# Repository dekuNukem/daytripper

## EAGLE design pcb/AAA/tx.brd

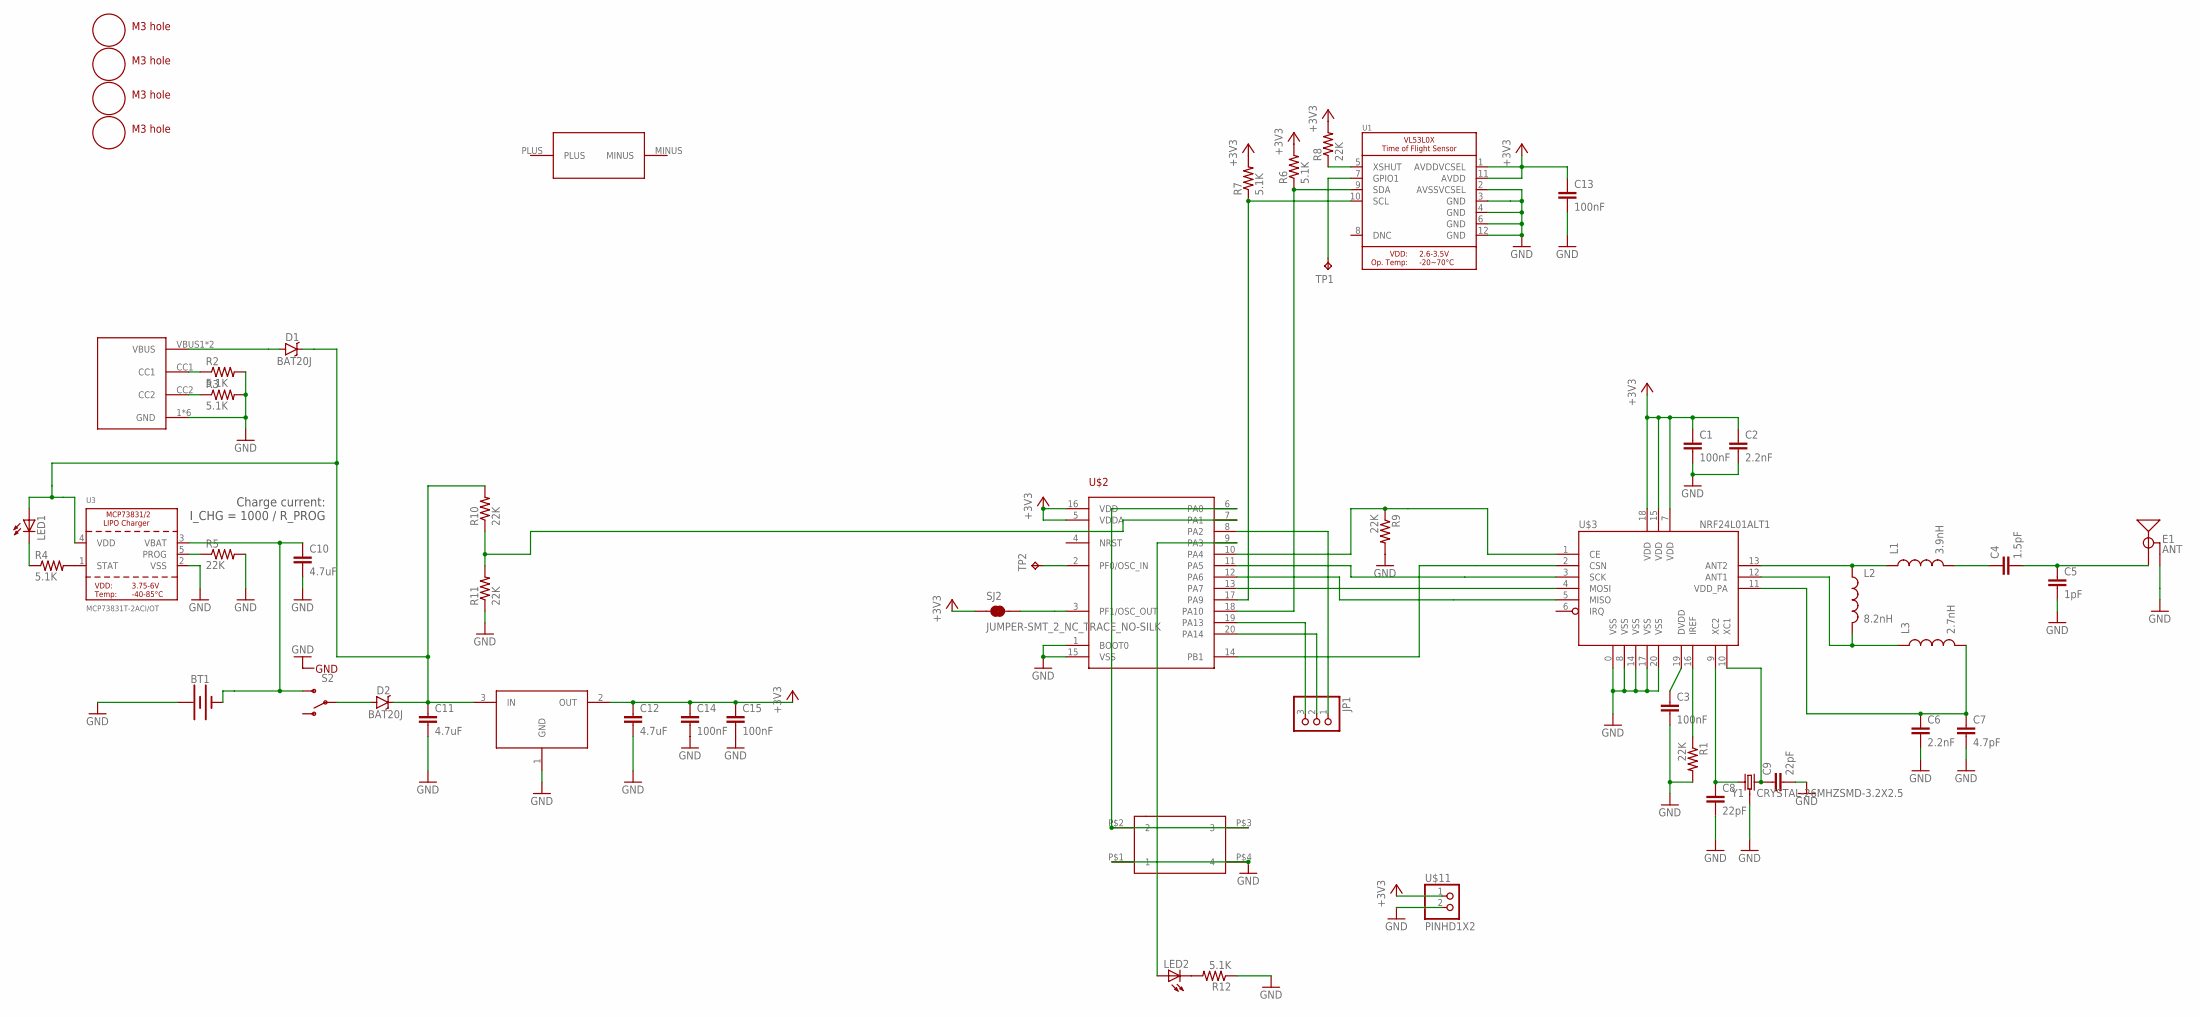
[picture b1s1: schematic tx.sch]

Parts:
BT1: TX_SPARKFUN-BATTERIES_BATTERY-24.5MM_PTH; TX_SPARKFUN-BATTERIES_BATTCON_24.5MM_PTH
C1, C3, C13, C14, C15: 100nF; 0805
C2, C6: 2.2nF; 0805
C4: 1.5pF; 0805
C5: 1pF; 0805
C7: 4.7pF; 0805
C8, C9: 22pF; 0805
C10, C11, C12: 4.7uF; 0805
D1, D2: BAT20J; SOD-323
E1: ANT; TRACE_ANTENNA_2.4GHZ_15.2MM
JP1: PINHD-1X3CB; 1X03-CLEANBIG
L1: 3.9nH; 0805
L2: 8.2nH; 0805
L3: 2.7nH; 0805
LED1, LED2: LEDCHIP-LED0805; CHIP-LED0805
R1, R5, R8, R9, R10, R11: 22K; 0805
R2, R3, R4, R6, R7, R12: 5.1K; 0805
S2: SWITCH-SPDTTDFGDFG; SWITCH-SPST-SMD-A
SJ2: JUMPER-SMT_2_NC_TRACE_NO-SILK; SMT-JUMPER_2_NC_TRACE_NO-SILK
TP1, TP2: TPTP12R; TP12R
U1: VL53L0X; LGA12_ST
U3: MCP73831T-2ACI/OT; SOT23-5
U$1: L1_USBC_6P_DEV; L1_USBC_6P_PAC
U$2: STM32F030F4; TSSOP20
U$3: NRF24L01ALT1; QFN20_ALT1
U$4: AAA_SYM; AAAWTF
U$5, U$6, U$7, U$8: M3_MOUNTING_HOLE; M3_MOUNTING_HOLE_PACK
U$9: XC6206_DEV; SOT23R_INFINEON
U$10: 324_SW324_SWITCH_FOOT_HOLE; 342_SWICH_FOOT_HOLE
U$11: PINHD1X2; 1X02
Y1: CRYSTAL-26MHZSMD-3.2X2.5; CRYSTAL-SMD-3.2X2.5MM

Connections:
+3V3: C1.1, C2.1, C12.1, C13.1, C14.1, C15.1, R6.2, R7.2, R8.2, SJ2.1, U1.1 (AVDDVCSEL), U1.11 (AVDD), U$2.5 (VDDA), U$2.16 (VDD), U$3.7 (VDD), U$3.15 (VDD), U$3.18 (VDD), U$9.2 (OUT), U$11.1
GND: BT1.2 (+), C1.2, C2.2, C3.2, C5.2, C6.2, C7.2, C8.2, C9.2, C10.2, C11.2, C12.2, C13.2, C14.2, C15.2, E1.GND, R1.2, R2.2, R3.2, R5.2, R9.2, R11.1, R12.1, S2.G1 (GND), S2.G2 (GND), S2.G3 (GND), S2.G4 (GND), U1.2 (AVSSVCSEL), U1.3 (GND), U1.4 (GND), U1.6 (GND), U1.12 (GND), U3.2 (VSS), U$1.1 (GND), U$1.2 (GND), U$1.3 (GND), U$1.4 (GND), U$1.GND1 (GND), U$1.GND2 (GND), U$2.1 (BOOT0), U$2.15 (VSS), U$3.0 (VSS), U$3.8 (VSS), U$3.14 (VSS), U$3.17 (VSS), U$3.20 (VSS), U$9.1 (GND), U$10.P$1 (1), U$10.P$4 (4), U$11.2, Y1.2 (3), Y1.4 (3)
unnamed: C3.1, U$3.19 (DVDD)
unnamed: R1.1, U$3.16 (IREF)
unnamed: L1.1, L2.1, U$3.13 (ANT2)
unnamed: C4.1, L1.2
unnamed: C4.2, C5.1, E1.ANT (SIGNAL)
unnamed: L2.2, L3.1, U$3.12 (ANT1)
unnamed: C8.1, U$3.9 (XC2), Y1.1
unnamed: C6.1, C7.1, L3.2, U$3.11 (VDD_PA)
unnamed: C9.1, U$3.10 (XC1), Y1.3 (2)
unnamed: R3.1, U$1.CC2
unnamed: R2.1, U$1.CC1
unnamed: LED1.C, R4.1
unnamed: R4.2, U3.1 (STAT)
unnamed: U$2.13 (PA7), U$3.4 (MOSI)
unnamed: U$2.12 (PA6), U$3.5 (MISO)
unnamed: U$2.11 (PA5), U$3.3 (SCK)
unnamed: R5.1, U3.5 (PROG)
unnamed: R6.1, U1.9 (SDA), U$2.18 (PA10)
unnamed: D2.A, S2.2
unnamed: U$2.14 (PB1), U$3.2 (CSN)
unnamed: R9.1, U$2.10 (PA4), U$3.1 (CE)
unnamed: R7.1, U1.10 (SCL), U$2.17 (PA9)
unnamed: R8.1, U1.5 (XSHUT)
unnamed: BT1.1 (-), C10.1, S2.3 (S), U3.3 (VBAT)
unnamed: D1.A, U$1.VBUS1 (VBUS), U$1.VBUS2 (VBUS)
unnamed: C11.1, D1.C, D2.C, LED1.A, R10.2, U3.4 (VDD), U$9.3 (IN)
unnamed: LED2.C, R12.2
unnamed: LED2.A, U$2.9 (PA3)
unnamed: U$2.6 (PA0), U$10.P$2 (2), U$10.P$3 (3)
unnamed: JP1.3, U$2.19 (PA13)
unnamed: JP1.2, U$2.20 (PA14)
unnamed: JP1.1, U$2.8 (PA2)
unnamed: SJ2.2, U$2.3 (PF1/OSC_OUT)
unnamed: R10.1, R11.2, U$2.7 (PA1)
unnamed: TP1.TP, U1.7 (GPIO1)
unnamed: TP2.TP, U$2.2 (PF0/OSC_IN)

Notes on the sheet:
Charge current: I_CHG = 1000 / R_PROG

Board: 2 copper layers, 55 parts (4 on the bottom side), 38 nets, no tracks yet.

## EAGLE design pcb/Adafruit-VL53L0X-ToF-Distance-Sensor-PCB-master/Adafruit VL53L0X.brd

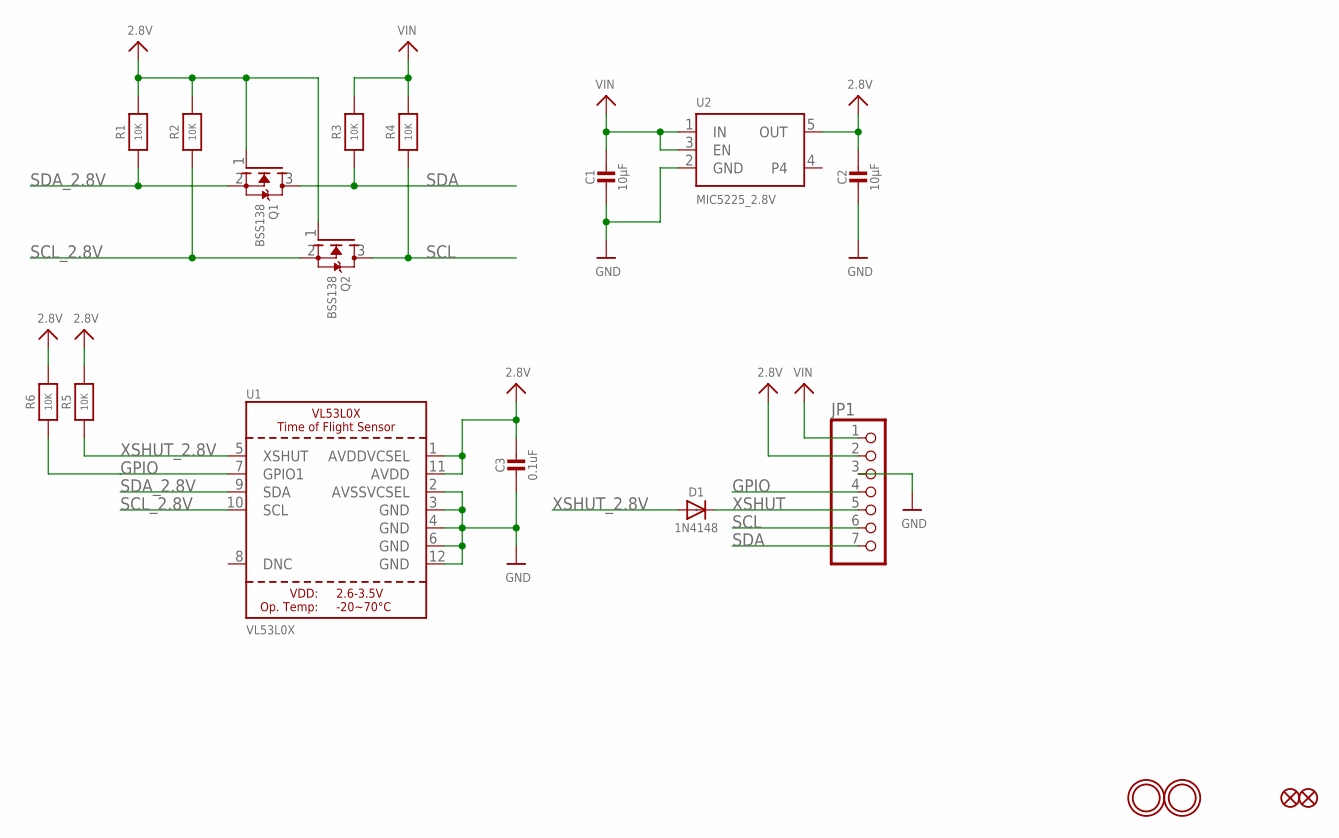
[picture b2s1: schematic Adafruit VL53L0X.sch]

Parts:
C1, C2: 10µF; 0805-NO
C3: 0.1uF; 0805-NO
D1: 1N4148; SOD-323
FID2, FID3: FIDUCIAL""; FIDUCIAL_1MM
JP1: HEADER-1X770MIL; 1X07_ROUND_70
Q1, Q2: BSS138; SOT23-WIDE
R1, R2, R3, R4, R5, R6: 10K; 0805-NO
U1: VL53L0X; LGA12_ST
U2: MIC5225_2.8V; SOT23-5
U$13, U$14: MOUNTINGHOLE2.5; MOUNTINGHOLE_2.5_PLATED

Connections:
2.8V: C2.1, C3.1, JP1.2, Q1.1 (G), Q2.1 (G), R1.2, R2.2, R5.2, R6.2, U1.1 (AVDDVCSEL), U1.11 (AVDD), U2.5 (OUT)
GND: C1.2, C2.2, C3.2, JP1.3, U1.2 (AVSSVCSEL), U1.3 (GND), U1.4 (GND), U1.6 (GND), U1.12 (GND), U2.2 (GND)
GPIO: JP1.4, R6.1, U1.7 (GPIO1)
SCL: JP1.6, Q2.3 (D), R4.1
SCL_2.8V: Q2.2 (S), R2.1, U1.10 (SCL)
SDA: JP1.7, Q1.3 (D), R3.1
SDA_2.8V: Q1.2 (S), R1.1, U1.9 (SDA)
VIN: C1.1, JP1.1, R3.2, R4.2, U2.1 (IN), U2.3 (EN)
XSHUT: D1.C, JP1.5
XSHUT_2.8V: D1.A, R5.1, U1.5 (XSHUT)

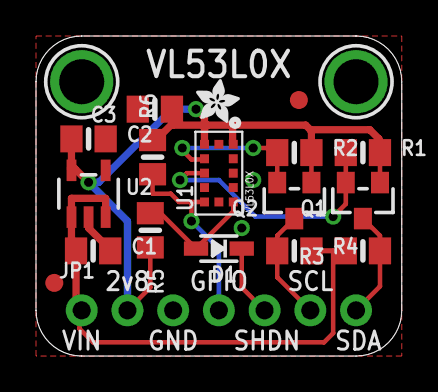
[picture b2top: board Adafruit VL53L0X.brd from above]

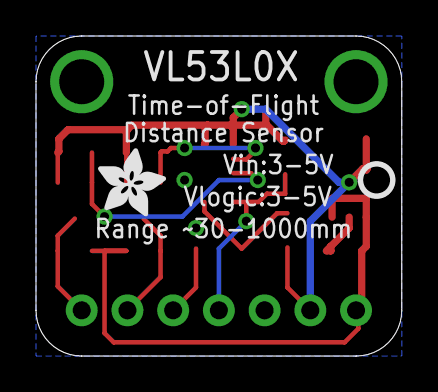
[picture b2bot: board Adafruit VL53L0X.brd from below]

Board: 2 copper layers, 20.3 x 17.8 mm, 22 parts (2 on the bottom side), 10 nets.

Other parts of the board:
U$12: PCBFEAT-REV-040
U$15: ADAFRUIT_3.5MM
U$18: ADAFRUIT_2.5MM

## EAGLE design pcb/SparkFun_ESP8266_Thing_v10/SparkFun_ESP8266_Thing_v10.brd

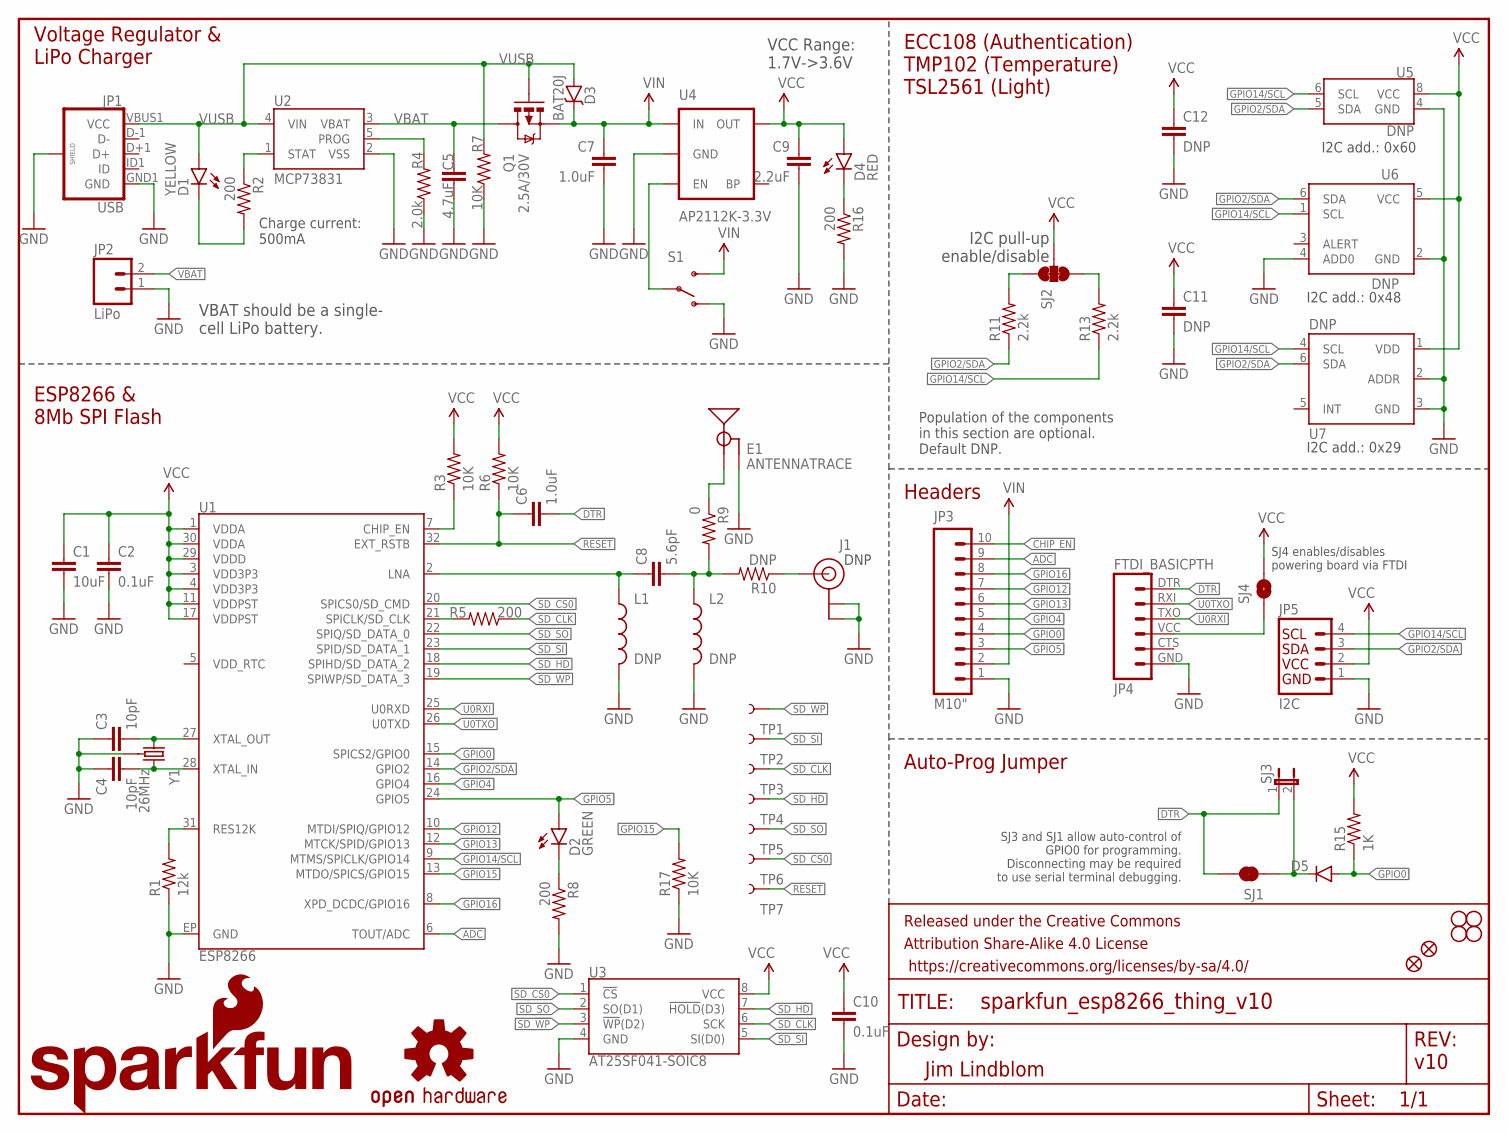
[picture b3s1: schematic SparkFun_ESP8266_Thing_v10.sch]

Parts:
C1: 10uF; 0603-CAP
C2, C10: 0.1uF; 0603-CAP
C3, C4: 10pF; 0603-CAP
C5: 4.7uF; 0603-CAP
C6: 1.0uF; 0603-CAP
C7: 1.0uF; 0805
C8: 5.6pF; 0603-CAP
C9: 2.2uF; 0603-CAP
C11, C12: DNP; 0603-CAP
D1: YELLOW; LED-0603
D2: GREEN; LED-0603
D3: BAT20J; SOD-323
D4: RED; LED-0603
D5: DIODEBAS16; SOD-323
E1: ANTENNATRACE; TRACE_ANTENNA_2.4GHZ_25.7MM
FID1, FID2: FIDUCIAL1X2; FIDUCIAL-1X2
FRAME1: FRAME-LETTER; CREATIVE_COMMONS
J1: DNP; U.FL
JP1: USB; USB-B-MICRO-SMD_V03
JP2: LiPo; JST-2-PTH
JP3: M10"; 1X10
JP4: FTDI_BASICPTH; FTDI_BASIC
JP5: I2C; 1X04
L1, L2: DNP; 0603
LOGO1: SFE_LOGO_NAME.2_INCH; SFE_LOGO_NAME_.2
LOGO3: SFE_LOGO_FLAME.1_INCH; SFE_LOGO_FLAME_.1
LOGO4: OSHW-LOGOS; OSHW-LOGO-S
Q1: 2.5A/30V; SOT23-3
R1: 12k; 0603-RES
R2, R5, R8, R16: 200; 0603-RES
R3, R6, R7, R17: 10K; 0603-RES
R4: 2.0k; 0603-RES
R9: 0; 0603
R10: DNP; 0603-RES
R11, R13: 2.2k; 0603-RES
R15: 1K; 0603-RES
S1: SWITCH-SPDT-SMD-A; SWITCH-SPST-SMD-A
SJ1: JUMPER-PAD-2-NC_BY_TRACE; PAD-JUMPER-2-NC_BY_TRACE_YES_SILK
SJ2: JUMPER-PAD-3-NC_BY_TRACE; PAD-JUMPER-3-3OF3_NC_BY_TRACE_YES_SILK_FULL_BOX
SJ3: JUMPER-PTH-2-NC; PTH-JUMPER-NC_BOTTOM_NO_SILK
SJ4: JUMPER-PAD-2-NOYES_SILK; PAD-JUMPER-2-NO_YES_SILK
STANDOFF1, STANDOFF2, STANDOFF3, STANDOFF4: STAND-OFF
TP1, TP2, TP3, TP4, TP5, TP6, TP7: TEST-POINT3X5; PAD.03X.05
U1: ESP8266; QFN32
U2: MCP73831; SOT23-5
U3: AT25SF041-SOIC8; SO08
U4: AP2112K-3.3V; SOT23-5
U5: DNP; UDFN8
U6: DNP; SOT563-2
U7: DNP; FN-6
Y1: 26MHz; CRYSTAL-SMD-3.2X2.5

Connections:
ADC: JP3.9, U1.6 (TOUT/ADC)
ANT: J1.P$3 (SIGNAL), R10.1
CHIP_EN: JP3.10, R3.1, U1.7 (CHIP_EN)
DTR: C6.2, JP4.DTR (1), SJ1.2, SJ3.1
FTDI_VCC: JP4.VCC (4), SJ4.1
GND: C1.2, C2.2, C3.1, C4.1, C5.2, C7.2, C9.2, C10.2, C11.2, C12.2, E1.GND, E1.GND2 (GND), J1.P$1 (GND), J1.P$2 (GND), JP1.GND1 (GND), JP1.SHIELD1 (SHIELD), JP1.SHIELD2 (SHIELD), JP1.SHIELD3 (SHIELD), JP2.1, JP3.1, JP4.GND (6), JP5.1, L1.2, L2.2, R1.1, R4.1, R7.1, R8.2, R16.2, R17.1, S1.1 (O), U1.EP (GND), U2.2 (VSS), U3.4 (GND), U4.2 (GND), U5.4 (GND), U6.2 (GND), U6.4 (ADD0), U7.2 (ADDR), U7.3 (GND), Y1.2 (GND), Y1.4 (GND)
GPIO0: D5.A, JP3.4, R15.1, U1.15 (SPICS2/GPIO0)
GPIO2/SDA: JP5.3, R11.1, U1.14 (GPIO2), U5.5 (SDA), U6.6 (SDA), U7.6 (SDA)
GPIO4: JP3.5, U1.16 (GPIO4)
GPIO5: D2.A, JP3.3, U1.24 (GPIO5)
GPIO12: JP3.7, U1.10 (MTDI/SPIQ/GPIO12)
GPIO13: JP3.6, U1.12 (MTCK/SPID/GPIO13)
GPIO14/SCL: JP5.4, R13.1, U1.9 (MTMS/SPICLK/GPIO14), U5.6 (SCL), U6.1 (SCL), U7.4 (SCL)
GPIO15: R17.2, U1.13 (MTDO/SPICS/GPIO15)
GPIO16: JP3.8, U1.8 (XPD_DCDC/GPIO16)
LNA: C8.1, L1.1, U1.2 (LNA)
unnamed: R1.2, U1.31 (RES12K)
unnamed: C4.2, U1.28 (XTAL_IN), Y1.3 (2)
unnamed: C3.2, U1.27 (XTAL_OUT), Y1.1
unnamed: D4.C, R16.1
unnamed: C8.2, L2.1, R9.2, R10.2
unnamed: R5.2, U1.21 (SPICLK/SD_CLK)
unnamed: D5.C, SJ1.1, SJ3.2
unnamed: R11.2, SJ2.1
unnamed: R13.2, SJ2.3
unnamed: S1.2, U4.3 (EN)
unnamed: R4.2, U2.5 (PROG)
unnamed: D2.C, R8.1
unnamed: D1.C, R2.2
unnamed: R2.1, U2.1 (STAT)
RESET: C6.1, R6.1, TP7.P$1, U1.32 (EXT_RSTB)
SD_!HD!: TP4.P$1, U1.18 (SPIHD/SD_DATA_2), U3.7 (!HOLD!(D3))
SD_!WP!: TP1.P$1, U1.19 (SPIWP/SD_DATA_3), U3.3 (!WP!(D2))
SD_CLK: R5.1, TP3.P$1, U3.6 (SCK)
SD_CS0: TP6.P$1, U1.20 (SPICS0/SD_CMD), U3.1 (!CS!)
SD_SI: TP2.P$1, U1.23 (SPID/SD_DATA_1), U3.5 (SI(D0))
SD_SO: TP5.P$1, U1.22 (SPIQ/SD_DATA_0), U3.2 (SO(D1))
TRACE_ANT: E1.ANT (SIGNAL), R9.1
U0RXI: JP4.TXO (3), U1.25 (U0RXD)
U0TXO: JP4.RXI (2), U1.26 (U0TXD)
VBAT: C5.1, JP2.2, Q1.3 (D), U2.3 (VBAT)
VCC: C1.1, C2.1, C9.1, C10.1, C11.1, C12.1, D4.A, JP5.2, R3.2, R6.2, R15.2, SJ2.2, SJ4.2, U1.1 (VDDA), U1.3 (VDD3P3), U1.4 (VDD3P3), U1.11 (VDDPST), U1.17 (VDDPST), U1.29 (VDDD), U1.30 (VDDA), U3.8 (VCC), U4.5 (OUT), U5.8 (VCC), U6.5 (VCC), U7.1 (VDD)
VIN: C7.1, D3.C, JP3.2, Q1.2 (S), S1.3 (S), U4.1 (IN)
VUSB: D1.A, D3.A, JP1.VBUS1 (VCC), Q1.1 (G), R7.2, U2.4 (VIN)

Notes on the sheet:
Jim Lindblom
ECC108 (Authentication) TMP102 (Temperature) TSL2561 (Light)
Voltage Regulator & LiPo Charger
ESP8266 & 8Mb SPI Flash
Headers
Auto-Prog Jumper
v10
VCC Range: 1.7V->3.6V
VBAT should be a single- cell LiPo battery.
I2C pull-up enable/disable
SJ4 enables/disables powering board via FTDI
SJ3 and SJ1 allow auto-control of GPIO0 for programming. Disconnecting may be required to use serial terminal debugging.
I2C add.: 0x48
I2C add.: 0x60
I2C add.: 0x29
Population of the components in this section are optional. Default DNP.
Charge current: 500mA
DNP

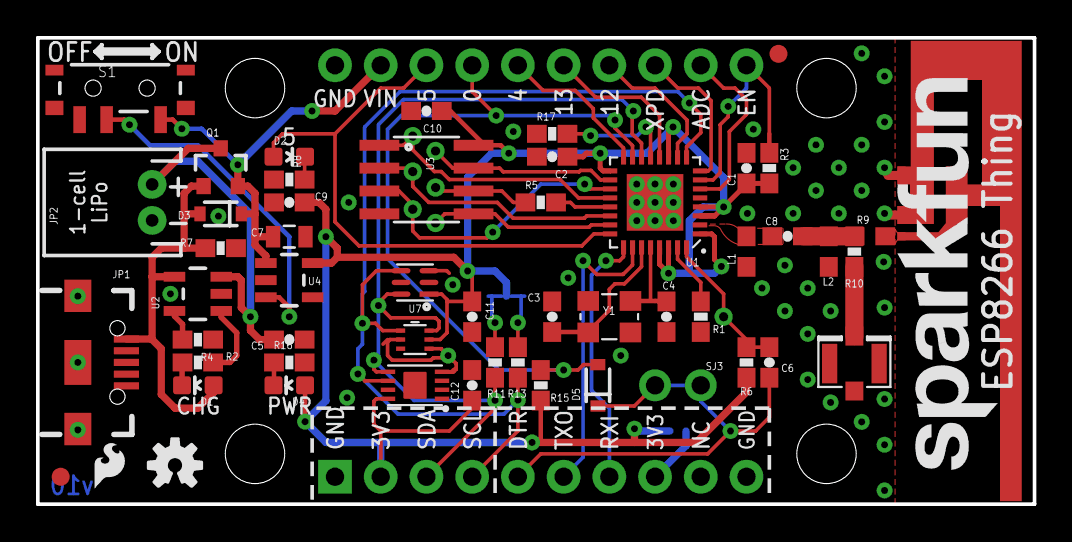
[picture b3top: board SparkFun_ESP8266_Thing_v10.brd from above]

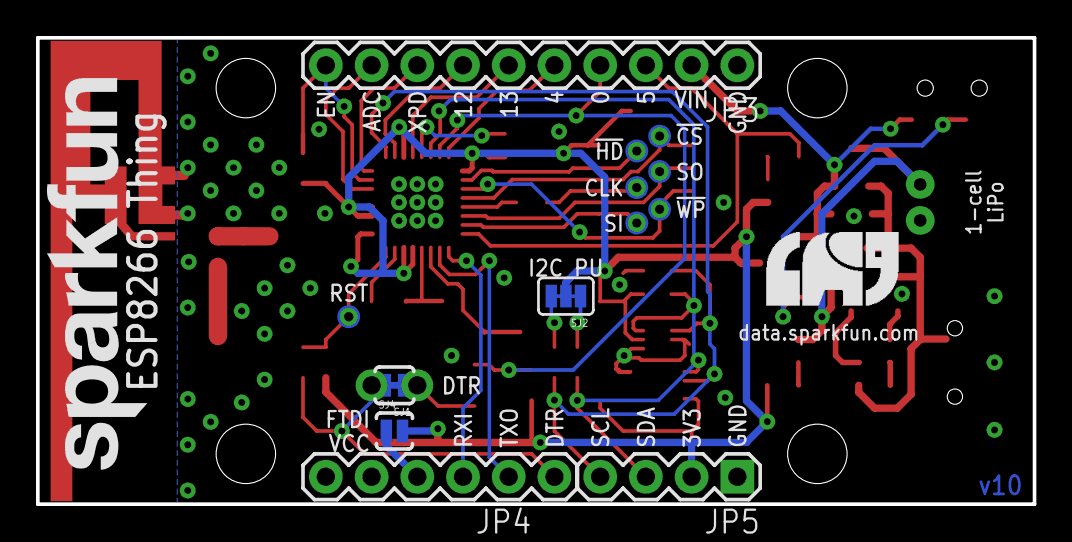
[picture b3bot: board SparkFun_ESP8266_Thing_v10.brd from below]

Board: 2 copper layers, 55.4 x 25.9 mm, 73 parts (14 on the bottom side), 44 nets.

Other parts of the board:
LOGO5: SFE_LOGO_NAME.2_INCH; SFE_LOGO_NAME_.2

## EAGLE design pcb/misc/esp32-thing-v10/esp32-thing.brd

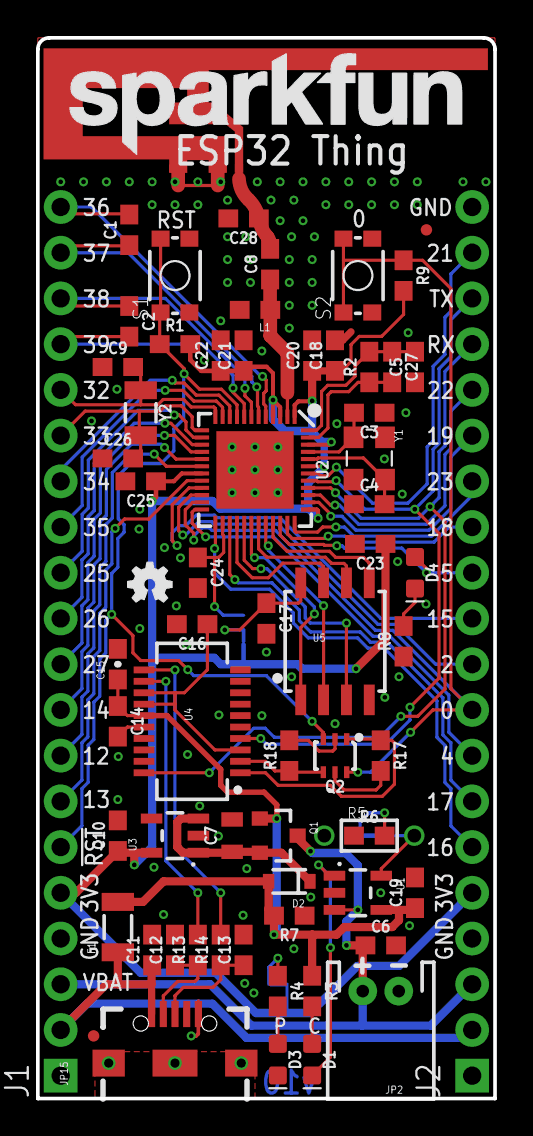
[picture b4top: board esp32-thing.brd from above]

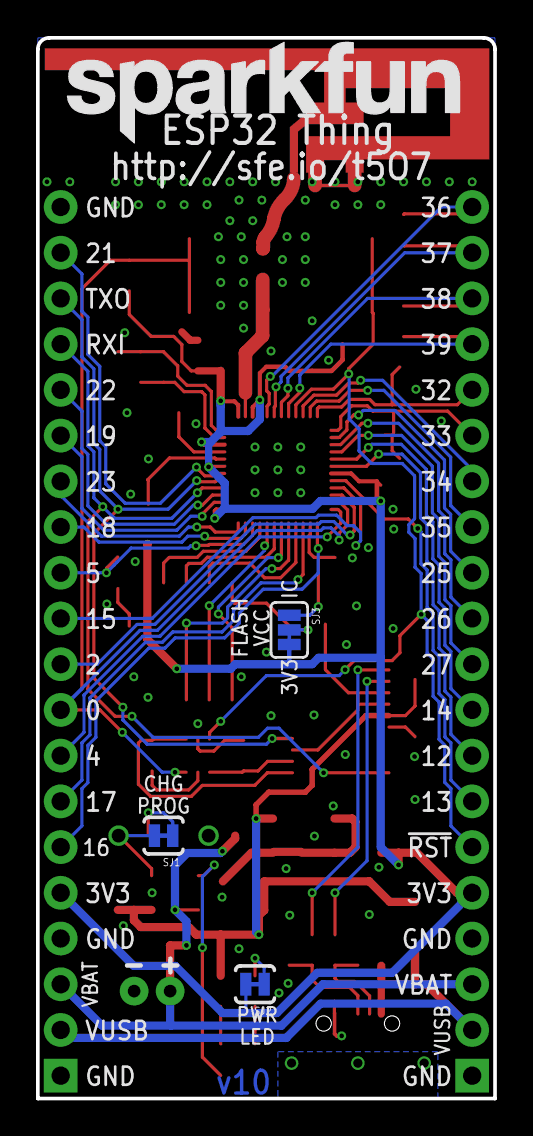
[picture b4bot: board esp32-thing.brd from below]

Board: 2 copper layers, 25.4 x 58.9 mm, 72 parts (4 on the bottom side), 66 nets.

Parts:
C1, C2: 270pF; 0603
C3, C4: 10pF; 0603
C5: 10nF; 0603
C6, C19: 4.7uF; 0603
C7: 1.0uF; 0805
C8: 5.6pF; 0603
C9, C26: 15pF; 0603
C10: 2.2uF; 0603
C11, C14, C16, C17, C20, C21, C23, C25: 0.1uF; 0603
C12, C13: 47pF; 0603
C15: 4.7uF; 0603-CAP
C18: 100pF; 0603
C22: 10uF; 0603
C24: 1.0uF; 0603
C27: 3.0nF; 0603
C28: 2.4pF; 0603
D1: Yellow; LED-0603
D2: BAT20J; SOD-323
D3: RED; LED-0603
D4: BLUE; LED-0603
E1: ANTENNA; TRACE_ANTENNA_2.4GHZ_25.7MM_TUNED
F1: 500mA; PTC-1206
FD1, FD2: FIDUCIALUFIDUCIAL; MICRO-FIDUCIAL
FRAME1: FRAME-LEDGER; CREATIVE_COMMONS
J1, J2: 1X20_NOSILK
JP2: LiPo; JST-2-PTH
JP15: USB-B-MICRO-SMD_V03
L1: 2.7nH; 0603
LOGO1, LOGO3: SFE_LOGO_NAME.2_INCH; SFE_LOGO_NAME_.2
LOGO2: OSHW-LOGOMINI; OSHW-LOGO-MINI
Q1: 2.5A/30V; SOT23-3
Q2: MBT3904DW1T1; SC70-6
R1, R7, R9, R17, R18: 10k; 0603
R2: 20k; 0603
R3, R4: 1K; 0603
R5: DNP; 1/6W-RES
R6: 2.0k; 0603
R8: 330; 0603
R13, R14: 27; 0603
S1: RESET; TACTILE_SWITCH_SMD_4.6X2.8MM
S2: BTN-0; TACTILE_SWITCH_SMD_4.6X2.8MM
SJ1, SJ2: JUMPER-PAD-2-NC_BY_TRACE; PAD-JUMPER-2-NC_BY_TRACE_YES_SILK
SJ3: PAD-JUMPER-3-2OF3_NC_BY_TRACE_YES_SILK_FULL_BOX
U1: MCP73831; SOT23-5
U2: ESP3212; QFN48-0.4MM
U3: AP2112K-3.3V; SOT23-5
U4: FT231XS; SSOP20_L
U5: W25Q32FVSS; SOIC-8
Y1: 26MHz; CRYSTAL-SMD-3.2X2.5
Y2: 32.768kHz; CRYSTAL-SMD-3.2X1.5MM

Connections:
0: J2.9, Q2.6, R9.1, S2.3, S2.4, U2.23
2: J2.10, U2.22
3.3V: C10.1, C18.1, C20.1, C21.1, C22.1, C23.1, C25.1, J1.5, J2.5, R1.2, R9.2, SJ2.2, SJ3.3, U2.1, U2.3, U2.4, U2.19, U2.37, U2.43, U2.46, U3.5
3.3V_F: C16.1, U4.3, U4.13, U4.14
4: J2.8, U2.24
5: D4.A, J2.12, U2.34
12: J1.8, U2.18
13: J1.7, U2.20
14: J1.9, U2.17
15: J2.11, U2.21
16: J2.6, U2.25
17: J2.7, U2.27
18: J2.13, U2.35
19: J2.15, U2.38
21: J2.19, U2.42
22: J2.16, U2.39
23: J2.14, U2.36
25: J1.12, U2.14
26: J1.11, U2.15
27: J1.10, U2.16
32K_XN: C26.2, J1.15, U2.13, Y2.P$2
32K_XP: C9.2, J1.16, U2.12, Y2.P$1
34: J1.14, U2.10
35: J1.13, U2.11
36: C1.2, J1.20, U2.5
37: C1.1, J1.19, U2.6
38: C2.1, J1.18, U2.7
39: C2.2, J1.17, U2.8
CAP_10N: C5.2, C27.1, R2.2, U2.48
CHIP_PU: J1.6, Q2.3, R1.1, S1.3, S1.4, U2.9
D+: C13.1, JP15.D+, R14.1
D-: C12.1, JP15.D-, R13.1
DTR: Q2.1, R17.1, U4.1
FLASH_SCK: U2.31, U5.6
FLASH_SCS: U2.30, U5.1
FLASH_SDI: U2.33, U5.5
FLASH_SDO: U2.32, U5.2
FLASH_SHD: U2.28, U5.7
FLASH_SWP: U2.29, U5.3
FLASH_VDD: C24.1, SJ3.1, U2.26
GND: C3.1, C4.1, C5.1, C6.2, C7.2, C9.1, C10.2, C11.2, C12.2, C13.2, C14.2, C15.2, C16.2, C17.2, C18.2, C19.2, C20.2, C21.2, C22.2, C23.2, C24.2, C25.2, C26.1, C28.2, D3.C, E1.GND, E1.GND2, J1.1, J1.4, J2.1, J2.4, J2.20, JP2.1, JP15.GND, L1.2, R5.1, R6.1, R7.1, R8.1, S1.1, S1.2, S2.1, S2.2, U1.2, U2.EP, U3.2, U4.6, U4.16, U5.4, Y1.2, Y1.4
LNA_IN: C8.1, L1.1, U2.2
unnamed: D4.C, R8.2
unnamed: D3.A, R4.2
unnamed: R4.1, SJ2.1
unnamed: C27.2, R2.1, U2.47
unnamed: R13.2, U4.12
unnamed: R14.2, U4.11
unnamed: D1.C, U1.1
unnamed: Q2.5, R17.2
unnamed: C17.1, SJ3.2, U5.8
unnamed: Q2.2, R18.2
unnamed: C3.2, U2.45, Y1.1
unnamed: R5.2, SJ1.2, U1.5
unnamed: C4.2, U2.44, Y1.3
unnamed: R6.2, SJ1.1
unnamed: D1.A, R3.2
RTS: Q2.4, R18.1, U4.2
SHIELD: JP15.SHIELD1, JP15.SHIELD2, JP15.SHIELD3
TRACE_ANT: C8.2, C28.1, E1.ANT
U0RXD: J2.17, U2.40, U4.20
U0TXD: J2.18, U2.41, U4.4
VIN: C7.1, D2.C, Q1.2, U3.1, U3.3
VUSB-RAW: C11.1, F1.1, J1.2, J2.2, JP15.VBUS
V_BATT: C6.1, J1.3, J2.3, JP2.2, Q1.3, U1.3
V_USB: C14.1, C15.1, C19.1, D2.A, F1.2, Q1.1, R3.1, R7.2, U1.4, U4.15

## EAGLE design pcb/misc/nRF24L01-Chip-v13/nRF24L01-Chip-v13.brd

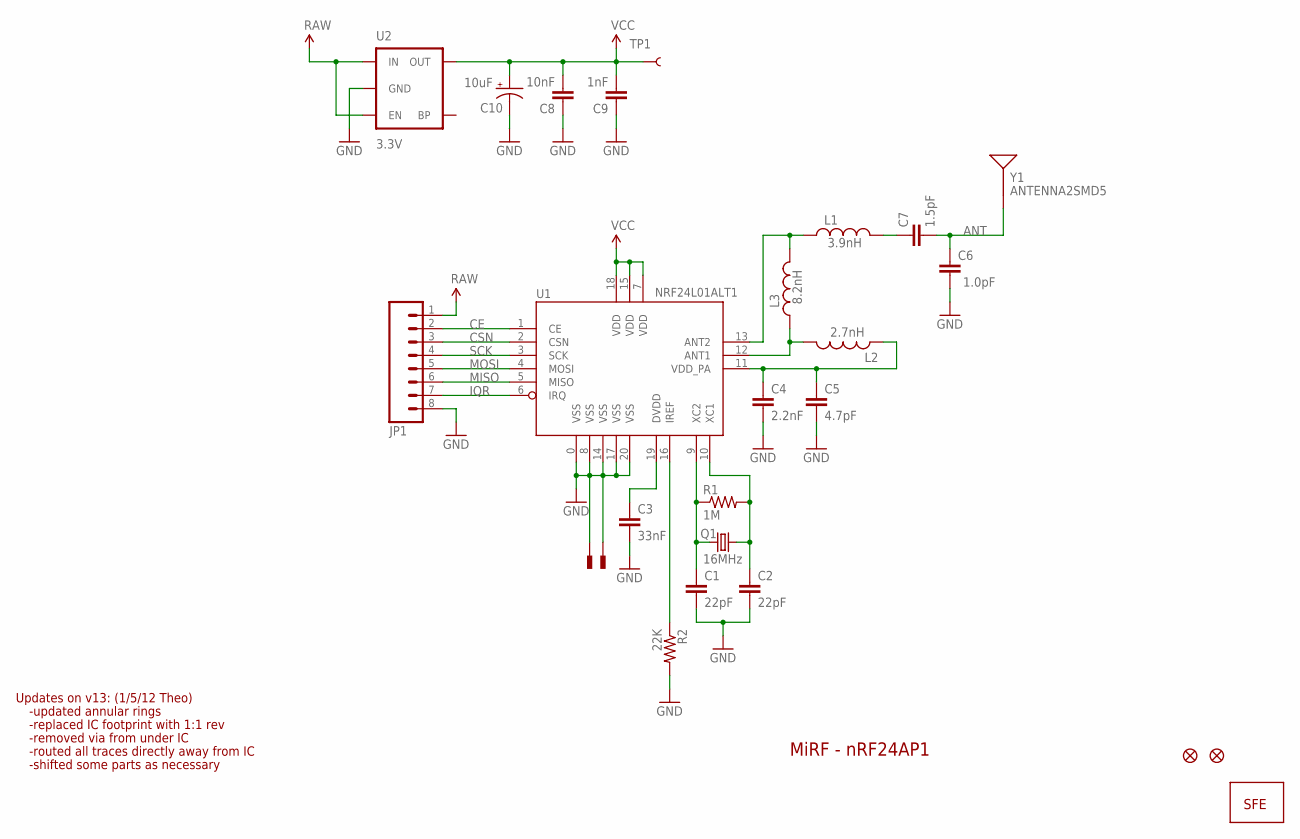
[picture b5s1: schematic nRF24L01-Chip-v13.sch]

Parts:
C1, C2: 22pF; 0402-CAP
C3: 33nF; 0402-CAP
C4: 2.2nF; 0402-CAP
C5: 4.7pF; 0402-CAP
C6: 1.0pF; 0402-CAP
C7: 1.5pF; 0402-CAP
C8: 10nF; 0402-CAP
C9: 1nF; 0402-CAP
C10: 10uF; EIA3216
JP1: M081X08; 1X08
JP2, JP3: FIDUCIALUFIDUCIAL; MICRO-FIDUCIAL
L1: 3.9nH; C0402
L2: 2.7nH; C0402
L3: 8.2nH; C0402
Q1: 16MHz; CRYSTAL-SMD-5X3
R1: 1M; 0402-RES
R2: 22K; 0402-RES
TP1: TEST-POINT3X5; PAD.03X.05
U1: NRF24L01ALT1; QFN20_ALT1
U2: 3.3V; SOT23-5
U$1, U$4: PAD; PAD-0.008
U$5: LOGO-SFENEW; SFE-NEW-WEBLOGO
Y1: ANTENNA2SMD5; ANTENNA-CHIP5

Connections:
ANT: C6.2, C7.2, Y1.FEED
CE: JP1.2, U1.1 (CE)
CSN: JP1.3, U1.2 (CSN)
GND: C1.2, C2.2, C3.2, C4.2, C5.2, C6.1, C8.1, C9.1, C10.C (-), JP1.8, R2.2, U1.0 (VSS), U1.8 (VSS), U1.14 (VSS), U1.17 (VSS), U1.20 (VSS), U2.2 (GND), U$1.P$1, U$4.P$1
IQR: JP1.7, U1.6 (IRQ)
MISO: JP1.6, U1.5 (MISO)
MOSI: JP1.5, U1.4 (MOSI)
unnamed: C1.1, Q1.1, R1.1, U1.9 (XC2)
unnamed: C2.1, Q1.3 (2), R1.2, U1.10 (XC1)
unnamed: L2.2, L3.1, U1.12 (ANT1)
unnamed: R2.1, U1.16 (IREF)
unnamed: C3.1, U1.19 (DVDD)
unnamed: L1.1, L3.2, U1.13 (ANT2)
unnamed: C4.1, C5.1, L2.1, U1.11 (VDD_PA)
unnamed: C7.1, L1.2
RAW: JP1.1, U2.1 (IN), U2.3 (EN)
SCK: JP1.4, U1.3 (SCK)
VCC: C8.2, C9.2, C10.A (+), TP1.P$1, U1.7 (VDD), U1.15 (VDD), U1.18 (VDD), U2.5 (OUT)

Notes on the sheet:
MiRF - nRF24AP1
Updates on v13: (1/5/12 Theo)
-updated annular rings
-replaced IC footprint with 1:1 rev
-removed via from under IC
-routed all traces directly away from IC
-shifted some parts as necessary

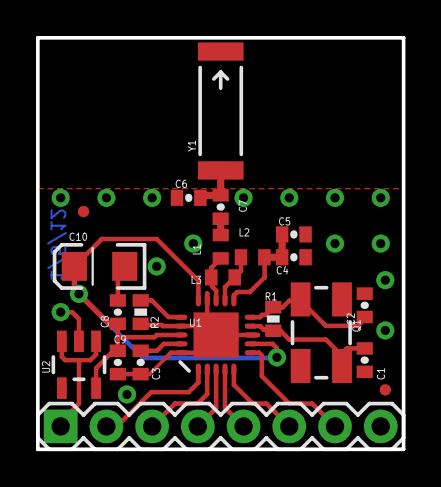
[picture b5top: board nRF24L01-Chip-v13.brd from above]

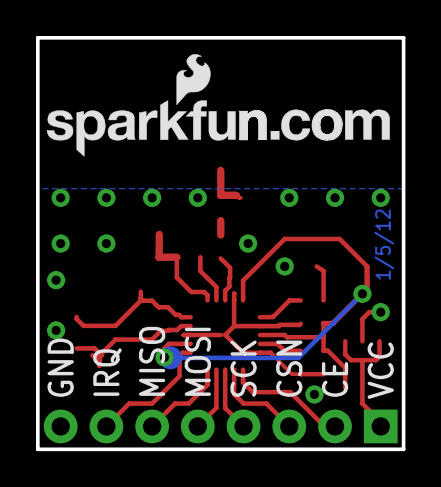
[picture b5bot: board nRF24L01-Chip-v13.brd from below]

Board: 2 copper layers, 20.3 x 22.9 mm, 26 parts (2 on the bottom side), 18 nets.

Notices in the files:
parts and their libraries:
SparkFun-Clocks: Licensing: Creative Commons ShareAlike 4.0 International - https://creativecommons.org/licenses/by-sa/4.0
microbuilder: This work is placed in the public domain, and may be freely used for commercial and non-commercial work with the following conditions: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
